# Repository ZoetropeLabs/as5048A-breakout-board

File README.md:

A breakout boad for the AS5048A angle sensor.

More information can be found [here](http://zoetrope.io/as5048).

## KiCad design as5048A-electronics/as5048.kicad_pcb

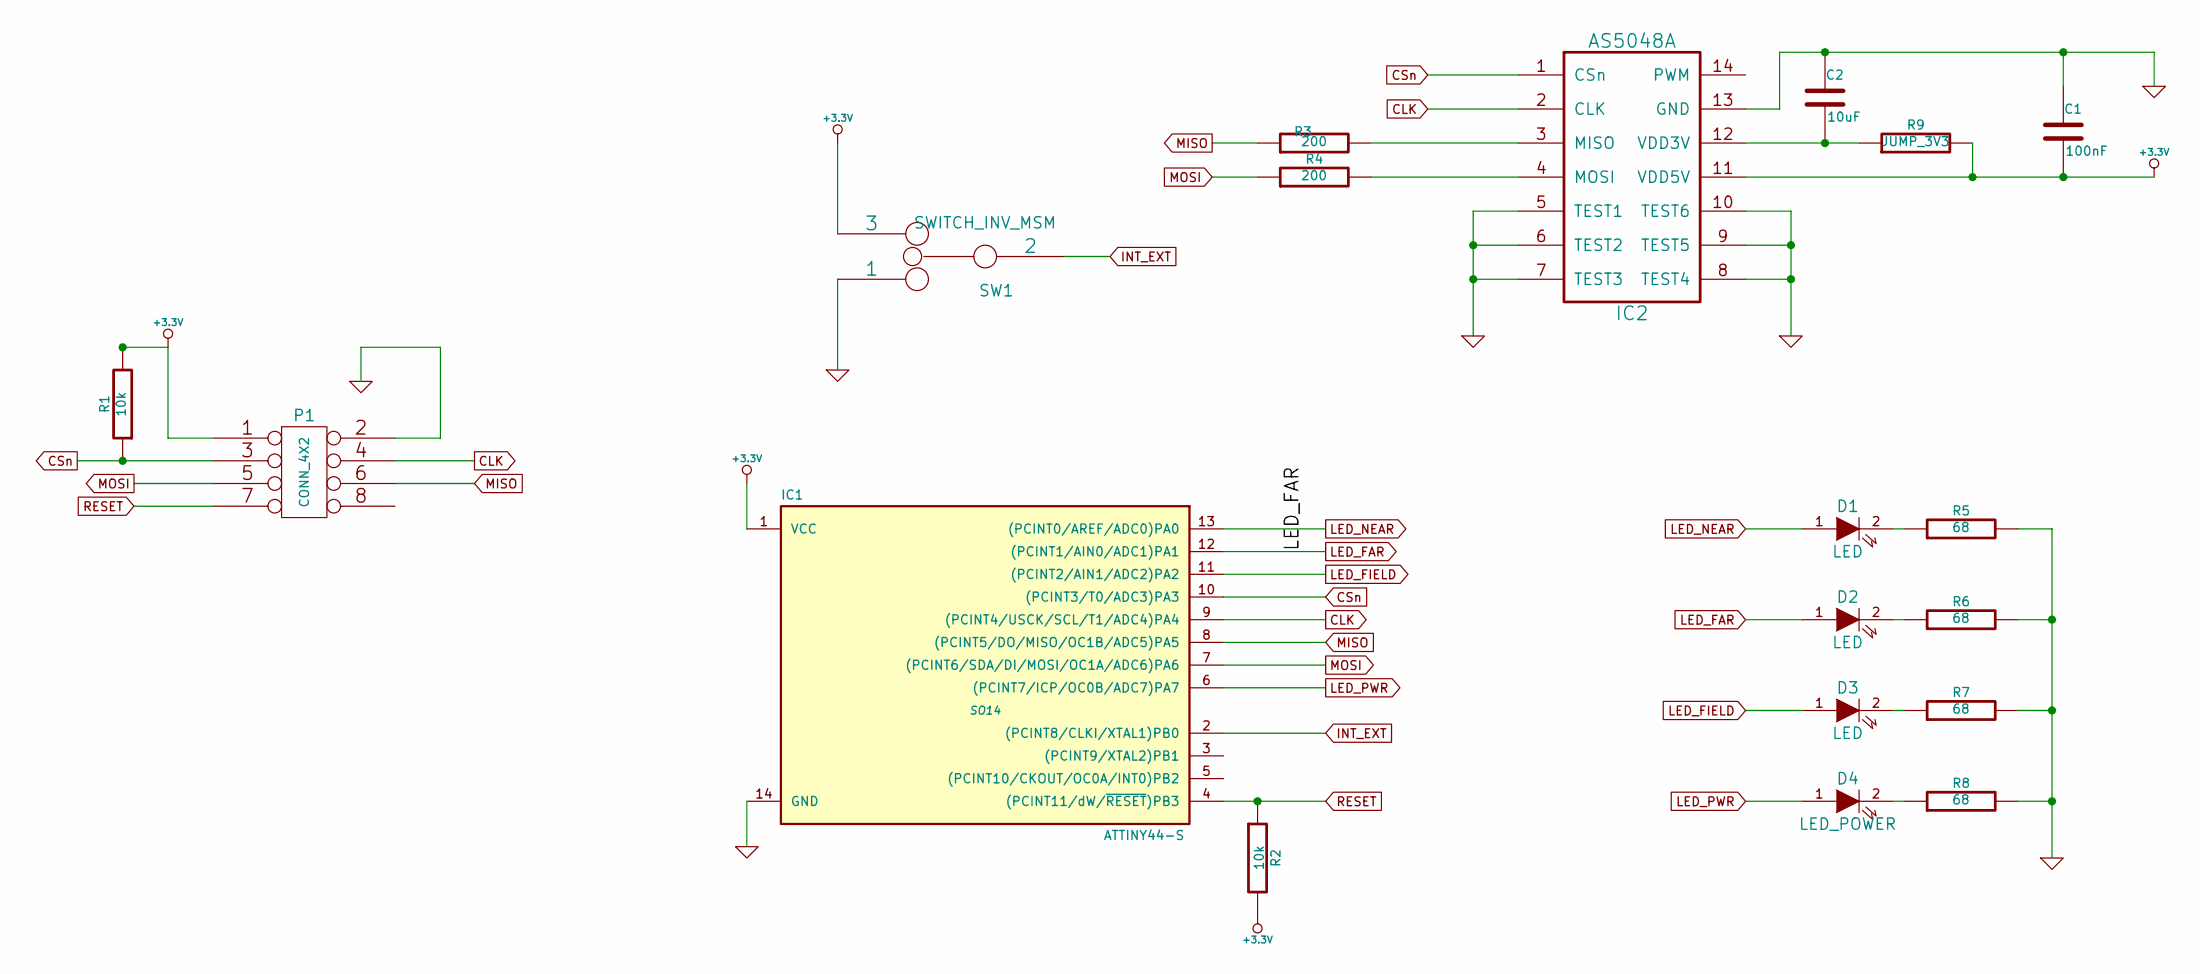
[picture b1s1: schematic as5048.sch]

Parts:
C1: 100nF
C2: 10uF
D1, D2, D3: LED
D4: LED_POWER
IC1: ATTINY44-S; SO14
IC2: AS5048A
P1: CONN_4X2
R1, R2: 10k
R3, R4: 200
R5, R6, R7, R8: 68
R9: JUMP_3V3
SW1: SWITCH_INV_MSM

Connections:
+3.3V: C1.2, IC1.1 (VCC), IC2.11 (VDD5V), P1.1, R1.2, R2.2, R9.2, SW1.3
CLK: IC1.9 ((PCINT4/USCK/SCL/T1/ADC4)PA4), IC2.2 (CLK), P1.4
CSn: IC1.10 ((PCINT3/T0/ADC3)PA3), IC2.1 (CSn), P1.3, R1.1
GND: C1.1, C2.1, IC1.14 (GND), IC2.5 (TEST1), IC2.6 (TEST2), IC2.7 (TEST3), IC2.8 (TEST4), IC2.9 (TEST5), IC2.10 (TEST6), IC2.13 (GND), P1.2, R5.2, R6.2, R7.2, R8.2, SW1.1
INT_EXT: IC1.2 ((PCINT8/CLKI/XTAL1)PB0), SW1.2
LED_FAR: D2.1 (A), IC1.12 ((PCINT1/AIN0/ADC1)PA1)
LED_FIELD: D3.1 (A), IC1.11 ((PCINT2/AIN1/ADC2)PA2)
LED_NEAR: D1.1 (A), IC1.13 ((PCINT0/AREF/ADC0)PA0)
LED_PWR: D4.1 (A), IC1.6 ((PCINT7/ICP/OC0B/ADC7)PA7)
MISO: IC1.8 ((PCINT5/DO/MISO/OC1B/ADC5)PA5), P1.6, R3.1
MOSI: IC1.7 ((PCINT6/SDA/DI/MOSI/OC1A/ADC6)PA6), P1.5, R4.1
unnamed: IC2.3 (MISO), R3.2
unnamed: IC2.4 (MOSI), R4.2
unnamed: D4.2 (K), R8.1
unnamed: D1.2 (K), R5.1
unnamed: D2.2 (K), R6.1
unnamed: D3.2 (K), R7.1
unnamed: C2.2, IC2.12 (VDD3V), R9.1
RESET: IC1.4 ((PCINT11/dW/~RESET~)PB3), P1.7, R2.1

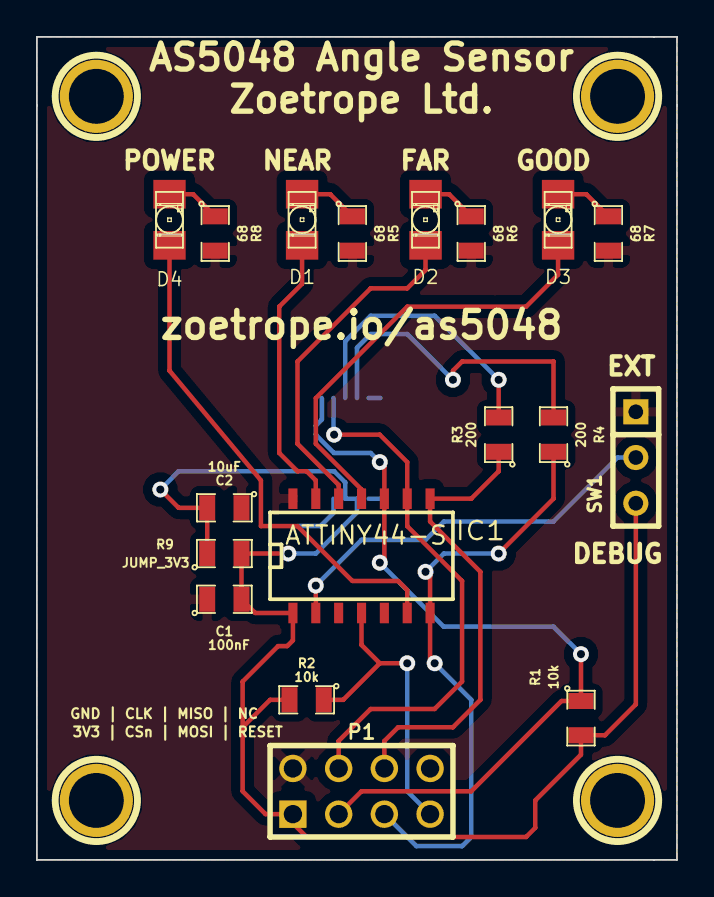
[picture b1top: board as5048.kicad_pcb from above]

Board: 2 copper layers, 35.6 x 45.7 mm, 23 parts (1 on the bottom side), 19 nets.

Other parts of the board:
1PIN, 1PIN#2, 1PIN#3, 1PIN#4: P***; 1pin

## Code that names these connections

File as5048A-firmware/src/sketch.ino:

/*
 *				ATMEL ATTINY44 / ARDUINO
 *
 *                          +-\/-+
 *                    VCC  1|    |14  GND
 *            (D 10)  PB0  2|    |13  AREF (D  0)
 *            (D  9)  PB1  3|    |12  PA1  (D  1) 
 *                    PB3  4|    |11  PA2  (D  2) 
 * PWM  INT0  (D  8)  PB2  5|    |10  PA3  (D  3) 
 * PWM        (D  7)  PA7  6|    |9   PA4  (D  4) 
 * PWM        (D  6)  PA6  7|    |8   PA5  (D  5)        PWM*
 *
 * Mappings for Angle Sensor Board (referenced against arduino pins)
 * 0 : LED NEAR
 * 1 : LED_FAR
 * 2 : LED FIELD
 * 3 : CSn
 * 4 : CLK
 * 5 : MISO
 * 6 : MOSI
 * 7 : NC
 * 8 : NC
 * 9 : NC
 * 10 : Internal/External Switch
 *
 */

#include <AS5048A.h>

#define LED_POWER 7
#define LED_NEAR 1
#define LED_FAR 0
#define LED_GOOD 2
#define ANGLE_CSn 3
#define ANGLE_CLK 4
#define ANGLE_MISO 5
#define ANGLE_MOSI 6
#define INT_EXT_SW 10

AS5048A angleSensor(ANGLE_CSn, ANGLE_MOSI, ANGLE_MISO, ANGLE_CLK);
boolean diagnosticMode = false;
boolean errorState = false;
boolean switch_state = digitalRead(INT_EXT_SW);


void setup() {                
	//Initialize the LEDs as an output.
	pinMode(LED_NEAR, OUTPUT);     
	pinMode(LED_FAR, OUTPUT);     
	pinMode(LED_GOOD, OUTPUT);     
	pinMode(LED_POWER, OUTPUT);
	pinMode(INT_EXT_SW, INPUT);
	digitalWrite(LED_POWER, 1);
	delay(300);
	digitalWrite(LED_FAR, 1);
	delay(300);
	digitalWrite(LED_NEAR, 1);
	delay(300);
	digitalWrite(LED_GOOD, 1);
	delay(300);
	digitalWrite(LED_NEAR, 0);
	digitalWrite(LED_GOOD, 0);
	digitalWrite(LED_FAR, 0);
	
	
	switch_state = !digitalRead(INT_EXT_SW);
	diagnosticMode = !switch_state;
	if (!diagnosticMode) {
		digitalWrite(LED_POWER,0);
		angleSensor.pause();
	}
		
}

void loop() {
	
	 switch_state = !digitalRead(INT_EXT_SW);

	if ((diagnosticMode) && (switch_state == true)) {
		digitalWrite(LED_NEAR, 0);
		digitalWrite(LED_GOOD, 0);
		digitalWrite(LED_FAR, 0);
		diagnosticMode = false;
		digitalWrite(LED_POWER,0);
		angleSensor.pause();
	}
	
	if ((!diagnosticMode) && (switch_state == false)) {
		diagnosticMode = true;
		digitalWrite(LED_POWER,1);
		angleSensor.restart();
	}

	if (diagnosticMode) {

		byte gain = angleSensor.getGain();

		errorState = false;//angleSensor.error();


		word state = angleSensor.getState();

		if (state & 0x400 || errorState) {
			digitalWrite(LED_FAR, 1);
		}
		else {
			digitalWrite(LED_FAR, 0);
		}

		if (state & 0x800 || errorState) {
			digitalWrite(LED_NEAR, 1);
		}
		else {
			digitalWrite(LED_NEAR, 0);
		}

		if (gain < 255 || errorState) {
			digitalWrite(LED_GOOD, 1);
		}
		else {
			digitalWrite(LED_GOOD, 0);
		}


	}

	delay(100);

}

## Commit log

2014-10-24 Add licence
2014-10-24 Update link in readme
2014-10-24 Added names to Licence
2014-10-27 Change link in README
2014-11-28 adding a basic openSCAD model
